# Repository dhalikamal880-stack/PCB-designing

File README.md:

# PCB-designing
My PCB design projects, KiCad files, schematics, Gerber files, and hardware documentation.

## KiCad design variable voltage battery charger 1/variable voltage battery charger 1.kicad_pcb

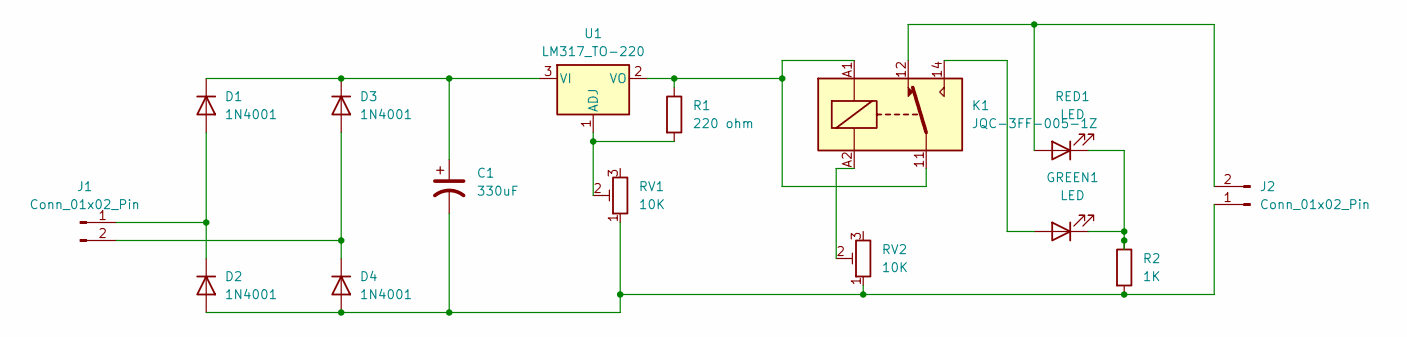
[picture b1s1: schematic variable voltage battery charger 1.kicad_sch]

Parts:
C1: 330uF; CP_Radial_D8.0mm_P5.00mm
D1, D2, D3, D4: 1N4001; D_DO-41_SOD81_P10.16mm_Horizontal
GREEN1: LED; LED_D3.0mm_Clear
J1, J2: Conn_01x02_Pin; PinSocket_1x02_P2.54mm_Vertical
K1: JQC-3FF-005-1Z; Relay_SPDT_Hongfa_JQC-3FF_0XX-1Z
R1: 220 ohm; R_Axial_DIN0207_L6.3mm_D2.5mm_P7.62mm_Horizontal
R2: 1K; R_Axial_DIN0207_L6.3mm_D2.5mm_P7.62mm_Horizontal
RED1: LED; LED_D3.0mm
RV1, RV2: 10K; Potentiometer_Bourns_3296W_Vertical
U1: LM317_TO-220; TO-220-3_Vertical

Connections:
unnamed: D1.2 (A), D2.1 (K), J1.1
unnamed: C1.1, D1.1 (K), D3.1 (K), U1.3 (VI)
unnamed: C1.2, D2.2 (A), D4.2 (A), J2.1, R2.2, RV1.1, RV2.1
unnamed: D3.2 (A), D4.1 (K), J1.2
unnamed: GREEN1.2 (A), K1.14
unnamed: GREEN1.1 (K), R2.1, RED1.1 (K)
unnamed: J2.2, K1.12, RED1.2 (A)
unnamed: K1.A2, RV2.2
unnamed: R1.2, RV1.2, U1.1 (ADJ)
unnamed: K1.11, K1.A1, R1.1, U1.2 (VO)

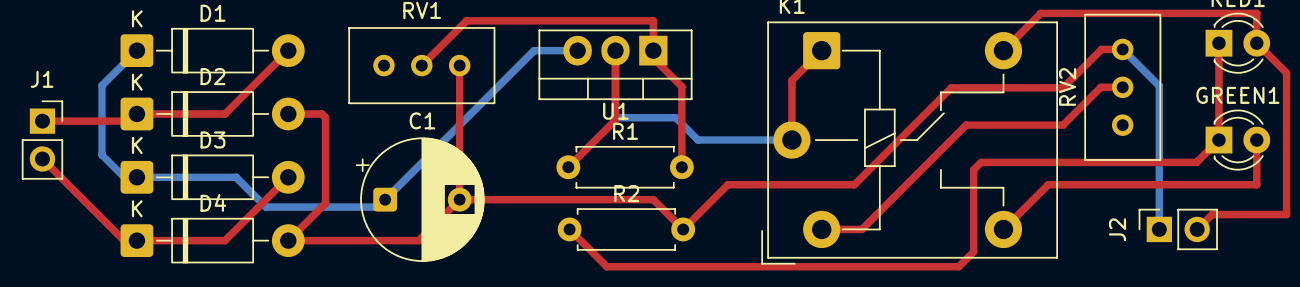
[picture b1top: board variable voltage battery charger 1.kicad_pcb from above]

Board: 2 copper layers, 15 parts (0 on the bottom side), 10 nets.

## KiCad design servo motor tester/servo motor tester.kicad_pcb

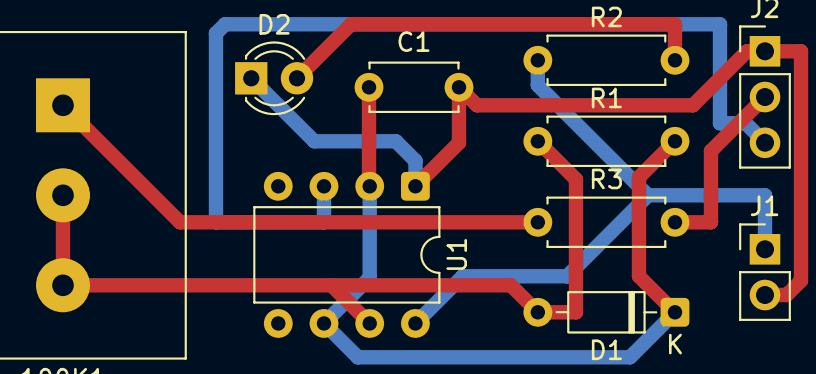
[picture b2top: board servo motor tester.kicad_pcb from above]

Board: 2 copper layers, 10 parts (0 on the bottom side), 8 nets.

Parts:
100K1: R_Potentiometer; Potentiometer_Alps_RK163_Single_Horizontal
C1: 22uF; C_Disc_D4.7mm_W2.5mm_P5.00mm
D1: 1n4148; D_DO-35_SOD27_P7.62mm_Horizontal
D2: LED; LED_D3.0mm
J1: Conn_01x02_Pin; PinHeader_1x02_P2.54mm_Vertical
J2: Conn_01x03_Pin; PinHeader_1x03_P2.54mm_Vertical
R1: 3M; R_Axial_DIN0207_L6.3mm_D2.5mm_P7.62mm_Horizontal
R2: 1k; R_Axial_DIN0207_L6.3mm_D2.5mm_P7.62mm_Horizontal
R3: 56K; R_Axial_DIN0207_L6.3mm_D2.5mm_P7.62mm_Horizontal
U1: NE555P; DIP-8_W7.62mm

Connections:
unnamed: 100K1.1, R3.1
unnamed: 100K1.2, 100K1.3, D1.2 (A), R1.1, U1.7 (DISCH)
unnamed: C1.1, D1.1 (K), R1.2, U1.2 (TRIG), U1.6 (THRES)
unnamed: D2.2 (A), R2.2
unnamed: C1.2, D2.1 (K), J1.2, J2.1, U1.1 (GND)
unnamed: J1.1, R2.1, U1.8 (VCC)
unnamed: J2.2, R3.2
unnamed: J2.3, U1.3 (OUT)

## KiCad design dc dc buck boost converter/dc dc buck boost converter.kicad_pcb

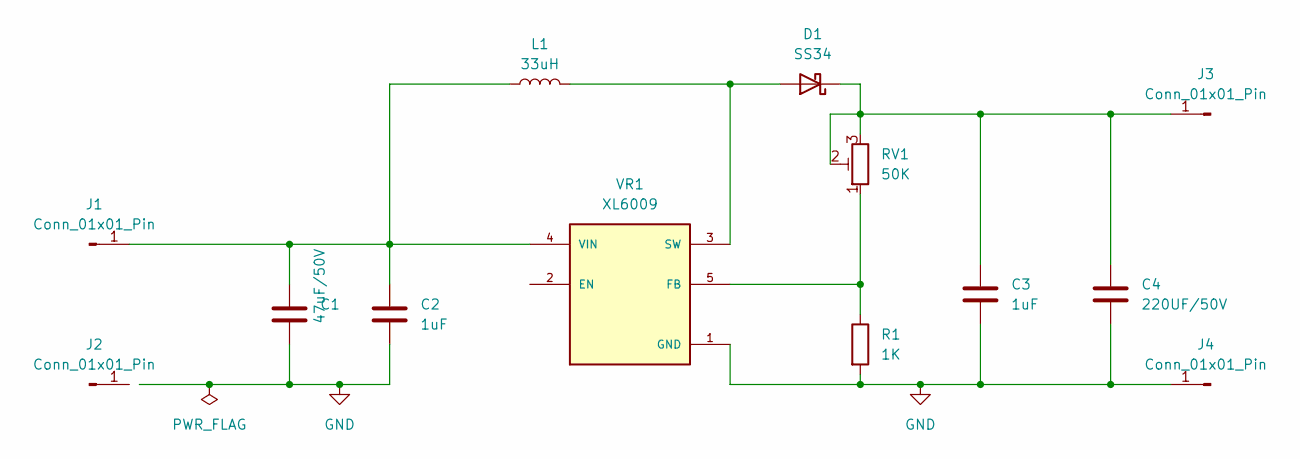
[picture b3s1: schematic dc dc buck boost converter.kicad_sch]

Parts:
C1: 47uF/50V; CP_Radial_D6.3mm_P2.50mm
C2, C3: 1uF; C_0805_2012Metric
C4: 220UF/50V; CP_Radial_D6.3mm_P2.50mm
D1: SS34; D_SMA
J1, J2, J3, J4: Conn_01x01_Pin; PinHeader_1x01_P2.54mm_Vertical
L1: 33uH; L_12x12mm_H8mm
R1: 1K; R_1206_3216Metric
RV1: 50K; Potentiometer_Bourns_3296W_Vertical
VR1: XL6009; DPAK170P1435X465-6N; PARTREV 1.1

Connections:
GND: C1.2, C2.2, C3.2, C4.2, J4.1 (Pin_1_1), R1.2, VR1.1 (GND)
unnamed: D1.2 (A), L1.2, VR1.3 (SW), VR1.6 (SW)
unnamed: C3.1, C4.1, D1.1 (K), J3.1 (Pin_1_1), RV1.2, RV1.3
unnamed: C1.1, C2.1, J1.1 (Pin_1_1), L1.1, VR1.4 (VIN)
unnamed: R1.1, RV1.1, VR1.5 (FB)

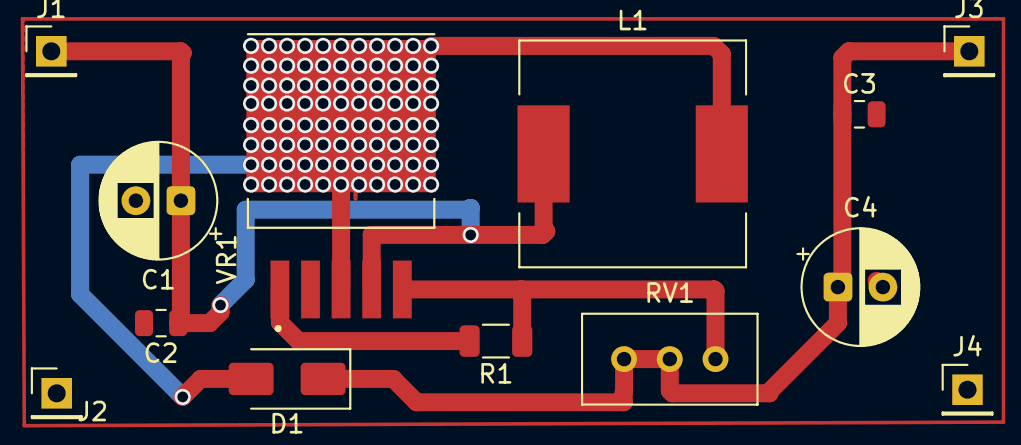
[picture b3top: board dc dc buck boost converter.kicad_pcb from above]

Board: 2 copper layers, 13 parts (0 on the bottom side), 5 nets.

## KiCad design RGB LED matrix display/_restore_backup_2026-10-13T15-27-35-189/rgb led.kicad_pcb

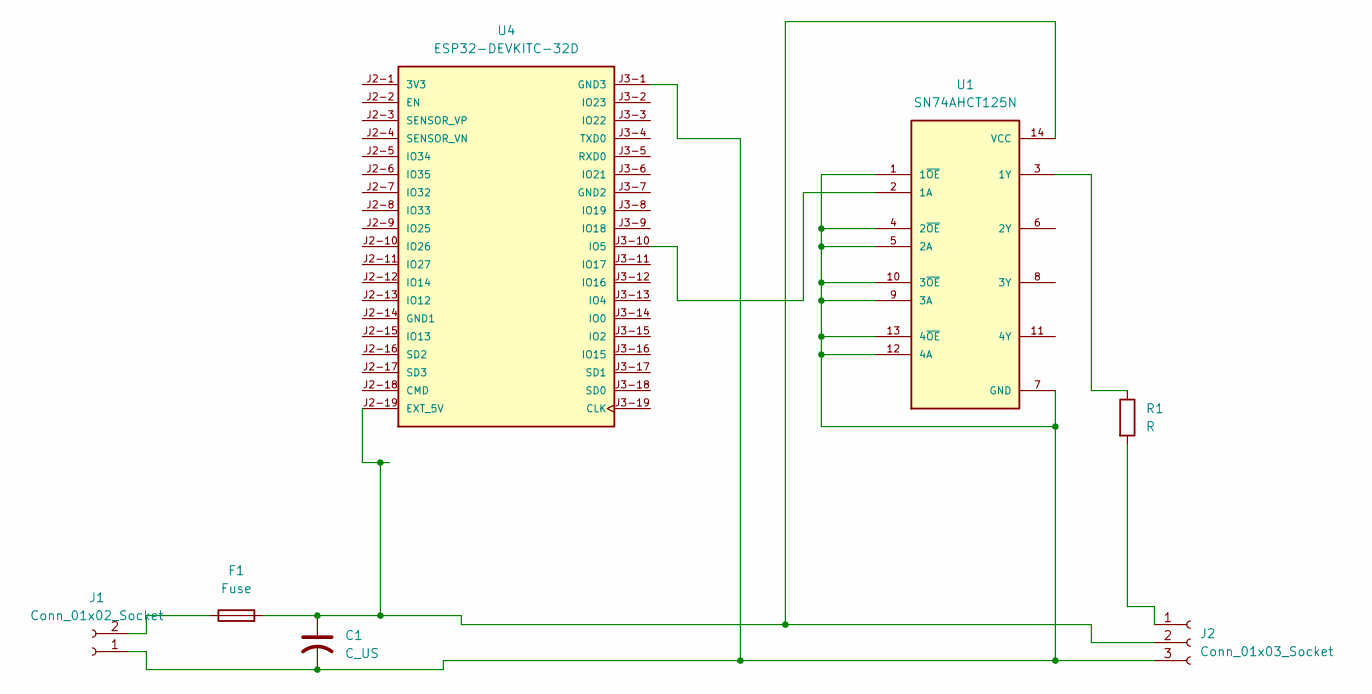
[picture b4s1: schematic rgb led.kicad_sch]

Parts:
C1: C_US; CP_Axial_L18.0mm_D10.0mm_P25.00mm_Horizontal
F1: Fuse; Fuse_Bourns_MF-RHT1300
J1: Conn_01x02_Socket; PinHeader_1x02_P2.00mm_Vertical
J2: Conn_01x03_Socket; PinHeader_1x03_P2.00mm_Vertical
R1: R; R_Axial_DIN0204_L3.6mm_D1.6mm_P1.90mm_Vertical
U1: SN74AHCT125N; DIP794W45P254L1930H508Q14; PARTREV Q
U4: ESP32-DEVKITC-32D; MODULE_ESP32-DEVKITC-32D; PARTREV V4

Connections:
unnamed: C1.2, J1.1, J2.3, U1.1 (1~OE), U1.4 (2~OE), U1.5 (2A), U1.7 (GND), U1.9 (3A), U1.10 (3~OE), U1.12 (4A), U1.13 (4~OE), U4.J3-1 (GND3)
unnamed: F1.1, J1.2
unnamed: J2.1, R1.2
unnamed: C1.1, F1.2, J2.2, U1.14 (VCC), U4.J2-19 (EXT_5V)
unnamed: U1.2 (1A), U4.J3-10 (IO5)
unnamed: R1.1, U1.3 (1Y)

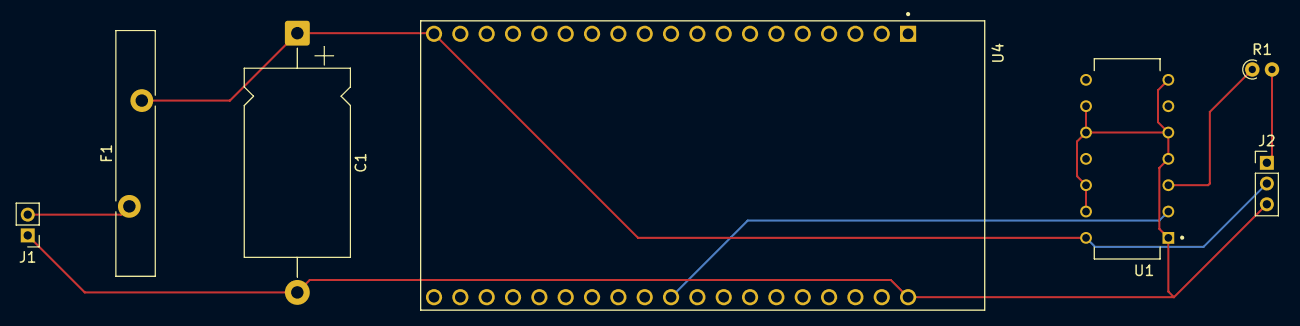
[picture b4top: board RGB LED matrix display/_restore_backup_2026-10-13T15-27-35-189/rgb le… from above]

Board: 2 copper layers, 7 parts (0 on the bottom side), 6 nets.

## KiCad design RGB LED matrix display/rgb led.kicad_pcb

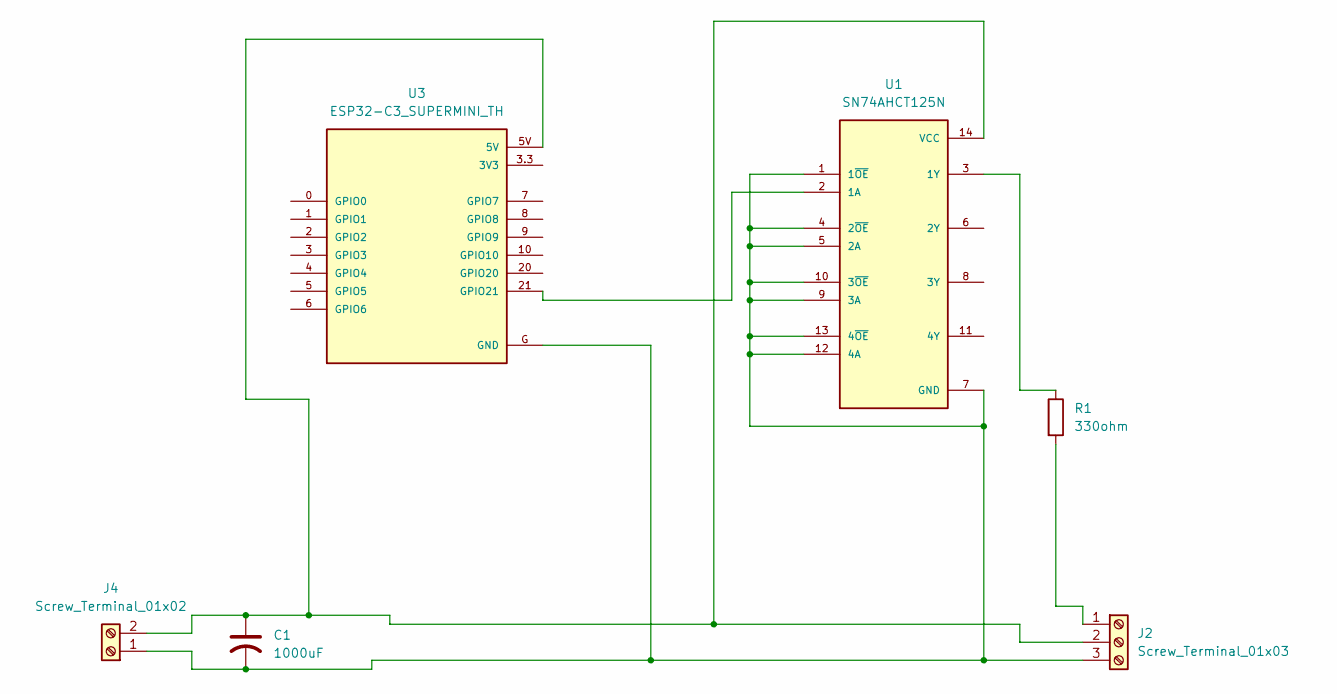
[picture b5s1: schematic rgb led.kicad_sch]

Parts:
C1: 1000uF; C_Radial_D10.0mm_H12.5mm_P5.00mm
J2: Screw_Terminal_01x03; TerminalBlock_Xinya_XY308-2.54-3P_1x03_P2.54mm_Horizontal
J4: Screw_Terminal_01x02; TerminalBlock_Xinya_XY308-2.54-2P_1x02_P2.54mm_Horizontal
R1: 330ohm; R_Axial_DIN0204_L3.6mm_D1.6mm_P1.90mm_Vertical
U1: SN74AHCT125N; DIP794W45P254L1930H508Q14; PARTREV Q
U3: ESP32-C3_SUPERMINI_TH; MODULE_ESP32-C3_SUPERMINI_TH

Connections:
unnamed: J2.1, R1.2
unnamed: C1.1, J2.2, J4.2, U1.14 (VCC), U3.5V
unnamed: C1.2, J2.3, J4.1, U1.1 (1~OE), U1.4 (2~OE), U1.5 (2A), U1.7 (GND), U1.9 (3A), U1.10 (3~OE), U1.12 (4A), U1.13 (4~OE), U3.G (GND)
unnamed: U1.2 (1A), U3.21 (GPIO21)
unnamed: R1.1, U1.3 (1Y)

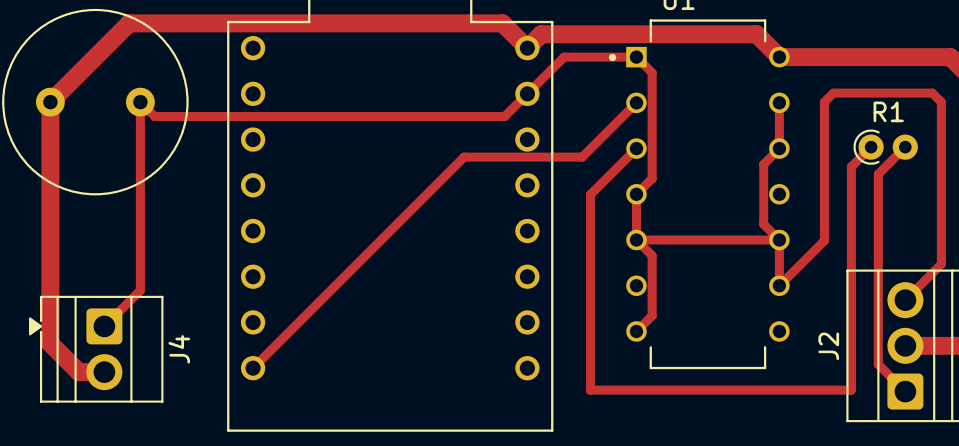
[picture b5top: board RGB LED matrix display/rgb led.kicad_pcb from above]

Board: 2 copper layers, 6 parts (0 on the bottom side), 5 nets.

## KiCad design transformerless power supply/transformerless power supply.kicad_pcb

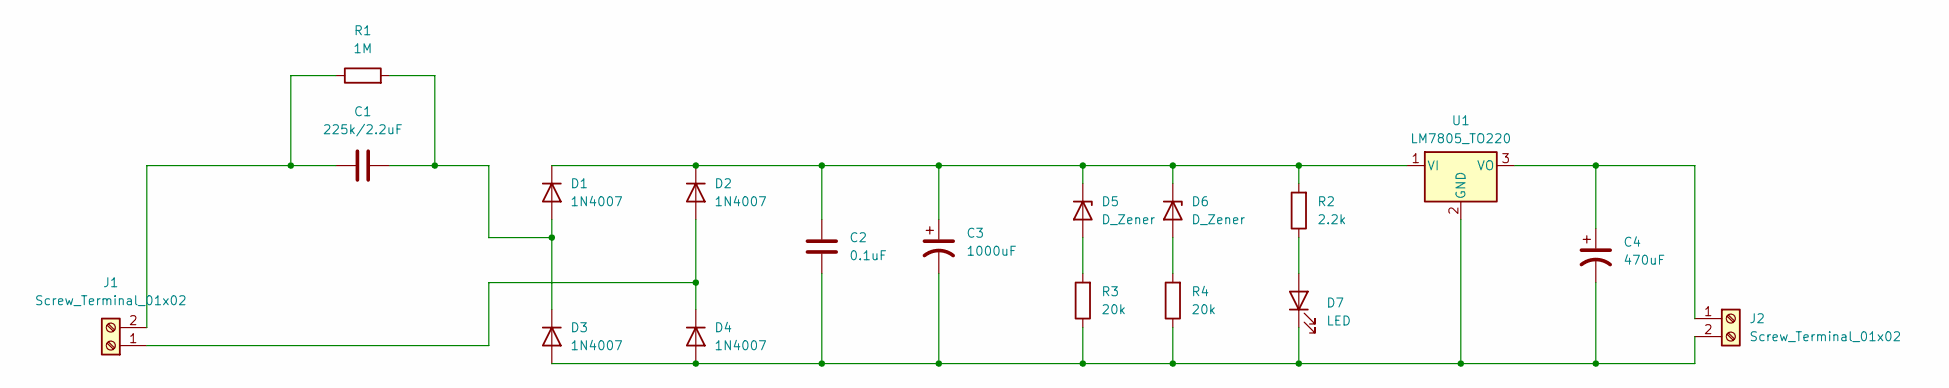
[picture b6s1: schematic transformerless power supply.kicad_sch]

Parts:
C1: 225k/2.2uF; C_Rect_L18.0mm_W7.0mm_P15.00mm_FKS3_FKP3
C2: 0.1uF; C_Disc_D4.3mm_W1.9mm_P5.00mm
C3: 1000uF; CP_Radial_D5.0mm_P2.00mm
C4: 470uF; CP_Radial_D5.0mm_P2.00mm
D1, D2, D3, D4: 1N4007; D_5W_P12.70mm_Horizontal
D5, D6: D_Zener; D_A-405_P7.62mm_Horizontal
D7: LED; LED_D3.0mm
J1, J2: Screw_Terminal_01x02; TerminalBlock_4Ucon_1x02_P3.50mm_Vertical
R1: 1M; R_Axial_DIN0207_L6.3mm_D2.5mm_P10.16mm_Horizontal
R2: 2.2k; R_Axial_DIN0207_L6.3mm_D2.5mm_P10.16mm_Horizontal
R3, R4: 20k; R_Axial_DIN0207_L6.3mm_D2.5mm_P10.16mm_Horizontal
U1: LM7805_TO220; TO-220-3_Vertical

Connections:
unnamed: C1.2, D1.2 (A), D3.1 (K), R1.2
unnamed: C2.2, C3.1, D1.1 (K), D2.1 (K), D5.1 (K), D6.1 (K), R2.2, U1.1 (VI)
unnamed: D2.2 (A), D4.1 (K), J1.1
unnamed: C2.1, C3.2, C4.2, D3.2 (A), D4.2 (A), D7.1 (K), J2.2, R3.1, R4.1, U1.2 (GND)
unnamed: D5.2 (A), R3.2
unnamed: D6.2 (A), R4.2
unnamed: D7.2 (A), R2.1
unnamed: C1.1, J1.2, R1.1
unnamed: C4.1, J2.1, U1.3 (VO)

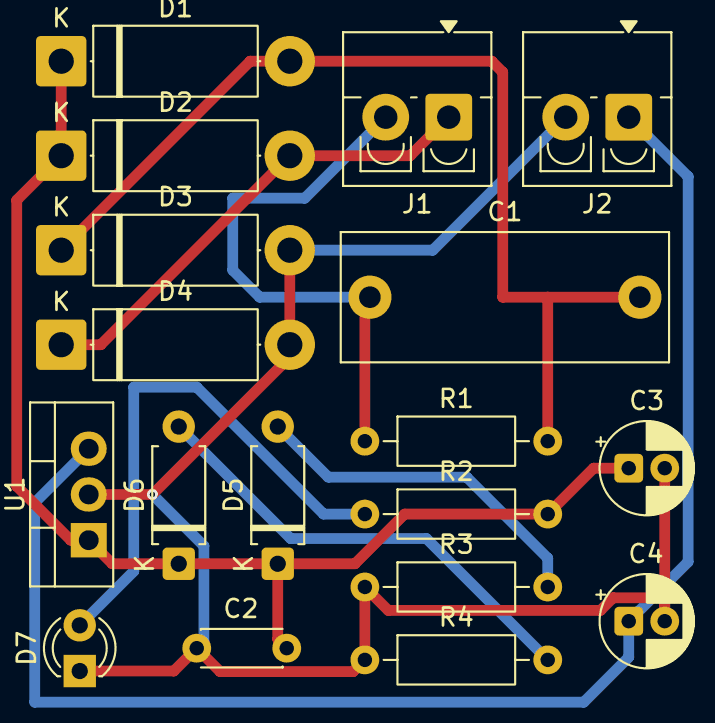
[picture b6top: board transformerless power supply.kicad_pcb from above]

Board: 2 copper layers, 18 parts (0 on the bottom side), 9 nets.
